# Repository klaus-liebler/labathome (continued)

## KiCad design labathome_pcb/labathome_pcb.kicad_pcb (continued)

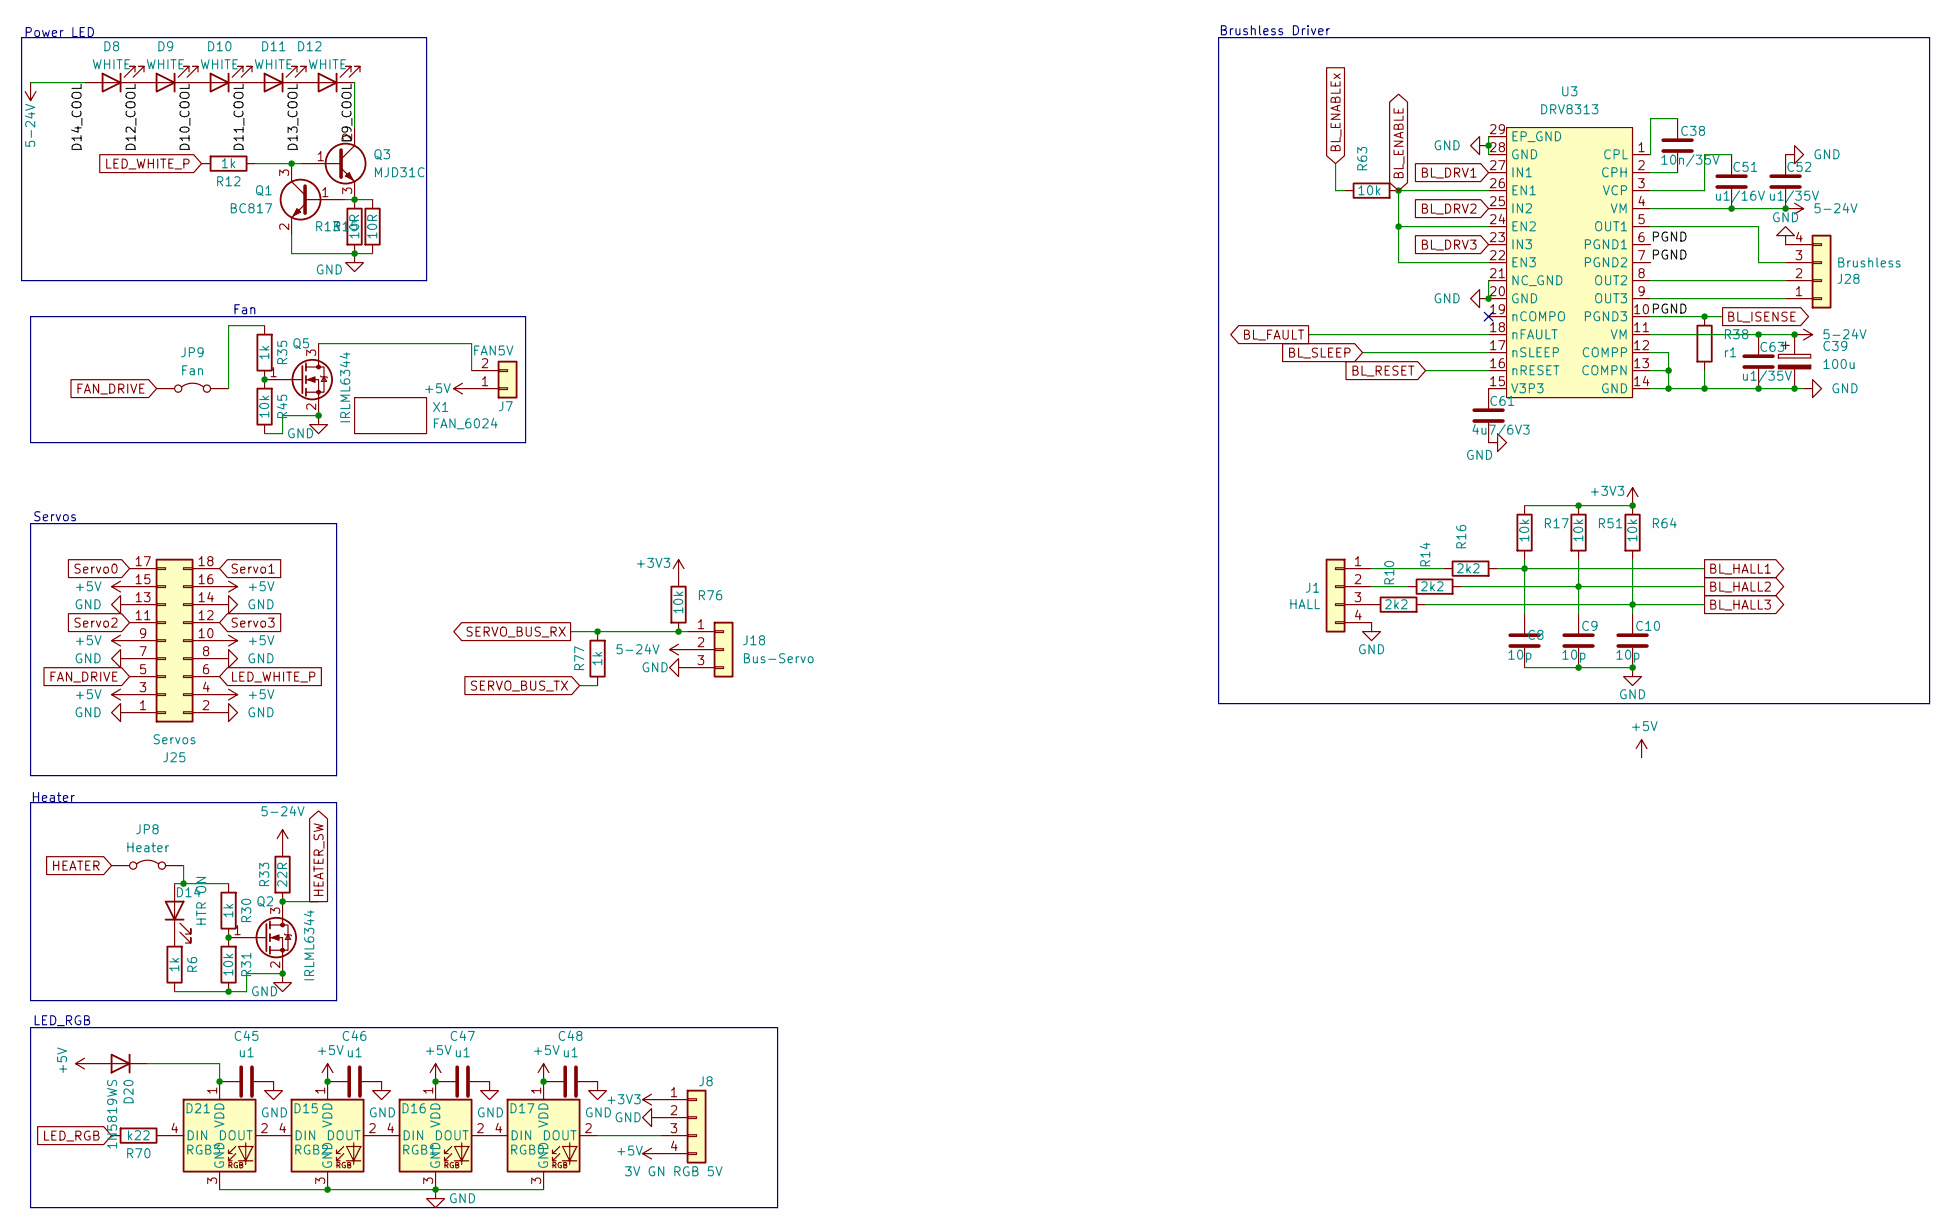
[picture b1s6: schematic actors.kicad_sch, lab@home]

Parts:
C8, C9, C10: 10p; C_0402_1005Metric; MPN CL05C100JB5NNNC
C38: 10n/35V; C_0402_1005Metric; MPN CL05B103KB5NNNC
C39: 100u; CP_Elec_6.3x5.4; MPN RST100UF35V009
C45, C46, C47, C48: u1; C_0201_0603Metric; MPN GRM033R61A104KE15D
C51: u1/16V; C_0603_1608Metric; MPN CC0603KRX7R9BB104
C52, C63: u1/35V; C_0603_1608Metric; MPN CC0603KRX7R9BB104
C61: 4u7/6V3; C_0402_1005Metric; MPN CL05A475MP5NRNC
D8, D9, D10, D11, D12: WHITE; LED_PLCC_2835_Handsoldering; MPN HL-A-2835D46W-S1-08-HR3(2800-3100K)
D14: HTR ON; LED_1206_3216Metric_ReverseMount; MPN LTST-C230KRKT
D15: RGB2; SK6812MINI-E_REV; MPN SK6812MINI-EA
D16: RGB1; SK6812MINI-E_REV; MPN SK6812MINI-EA
D17: RGB0; SK6812MINI-E_REV; MPN SK6812MINI-EA
D20: 1N5819WS; D_SOD-323; MPN 1N5819WS
D21: RGB3; SK6812MINI-E_REV; MPN SK6812MINI-EA
J1: HALL; PhoenixContact_MC_1,5_4-G-3.5_1x04_P3.50mm_Horizontal_small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; MPN KF2EDGR-3.5-4P
J7: FAN5V; JST_XH_B2B-XH-A_1x02_P2.50mm_Vertical; MPN B2B-XH-A(LF)(SN)
J8: 3V GN RGB 5V; PinHeader_1x04_P2.54mm_Vertical; MPN 2.54-1*4P
J18: Bus-Servo; Molex_SPOX_5267-03A_1x03_P2.50mm_Vertical; MPN 5267-03A / 22035035
J25: Servos; PinHeader_2x09_P2.54mm_Horizontal_SMD; MPN PZ254-2-09-WS
J28: Brushless; PhoenixContact_MC_1,5_4-G-3.5_1x04_P3.50mm_Horizontal_small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; MPN KF2EDGR-3.5-4P
JP8: Heater; SolderJumper-2_P1.3mm_Bridged2Bar_RoundedPad1.0x1.5mm
JP9: Fan; SolderJumper-2_P1.3mm_Bridged2Bar_RoundedPad1.0x1.5mm
Q1: BC817; SOT-23; MPN MMBT3904(RANGE:100-300)
Q2, Q5: IRLML6344; SOT-23; MPN AO3400
Q3: MJD31C; TO-252-2; MPN MJD31C
R6, R12, R30, R35: 1k; R_0402_1005Metric; MPN 0402WGF1001TCE
R10, R14, R16: 2k2; R_0402_1005Metric; MPN 0402WGF2201TCE
R13, R15: 10R; R_1206_3216Metric; MPN 1206W4F100JT5E
R17, R31, R45, R51, R63, R64: 10k; R_0201_0603Metric; MPN 0201WMF1002TEE
R33: 22R; Resistor_100W
R38: r1; R_1206_3216Metric; MPN FRM121WFR100TM
R70: k22; R_0402_1005Metric; MPN 0402WGF2200TCE
R76: 10k; R_0805_2012Metric_Pad1.20x1.40mm_HandSolder
R77: 1k; R_0805_2012Metric_Pad1.20x1.40mm_HandSolder
U3: DRV8313; HTSSOP-28-1EP_4.4x9.7mm_P0.65mm_EP2.85x5.4mm_ThermalVias; MPN DRV8313PWPR
X1: FAN_6024

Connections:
5-24V: C39.1, C51.2, C52.2, C63.1, D8.2 (A), J18.2, R33.1, U3.4 (VM), U3.11 (VM); also elsewhere on the board
+3V3: J8.1, R17.1, R51.1, R64.1, R76.1; also elsewhere on the board
+5V: C46.2, C47.2, C48.2, D15.1 (VDD), D16.1 (VDD), D17.1 (VDD), D20.2 (A), J7.1, J8.4, J25.3, J25.4, J25.9, J25.10, J25.15, J25.16; also elsewhere on the board
/actors/D9_COOL: D12.1 (K), Q3.2 (C)
/actors/D10_COOL: D9.1 (K), D10.2 (A)
/actors/D11_COOL: D10.1 (K), D11.2 (A)
/actors/D12_COOL: D8.1 (K), D9.2 (A)
/actors/D13_COOL: D11.1 (K), D12.2 (A)
ADC0_U1T: R77.1; also elsewhere on the board
ADC1_U1R: J18.1, R76.2, R77.2; also elsewhere on the board
BL_DRV1: U3.27 (IN1); also elsewhere on the board
BL_DRV2: U3.25 (IN2); also elsewhere on the board
BL_DRV3: U3.23 (IN3); also elsewhere on the board
BL_ENABLE: R63.2, U3.22 (EN3), U3.24 (EN2), U3.26 (EN1)
BL_ENABLEx: R63.1; also elsewhere on the board
BL_FAULT: U3.18 (nFAULT); also elsewhere on the board
BL_HALL1: C8.1, R16.2, R17.2; also elsewhere on the board
BL_HALL2: C9.1, R14.2, R51.2; also elsewhere on the board
BL_HALL3: C10.1, R10.2, R64.2; also elsewhere on the board
BL_ISENSE: R38.1, U3.6 (PGND1), U3.7 (PGND2), U3.10 (PGND3); also elsewhere on the board
BL_RESET: U3.16 (nRESET); also elsewhere on the board
BL_SLEEP: U3.17 (nSLEEP); also elsewhere on the board
FAN_DRIVE: J25.5, JP9.1 (A); also elsewhere on the board
GND: C8.2, C9.2, C10.2, C39.2, C45.1, C46.1, C47.1, C48.1, C52.1, C61.2, C63.2, D15.3 (GND), D16.3 (GND), D17.3 (GND), D21.3 (GND), J1.4, J8.2, J18.3, J25.1, J25.2, J25.7, J25.8, J25.13, J25.14, J28.4, Q1.2 (E), Q2.2 (S), Q5.2 (S), R6.1, R13.2, R15.2, R31.1, R38.2, R45.1, U3.12 (COMPP), U3.13 (COMPN), U3.14 (GND), U3.20 (GND), U3.21 (NC_GND), U3.28 (GND), U3.29 (EP_GND); also elsewhere on the board
HEATER: JP8.1 (A); also elsewhere on the board
HEATER_SW: Q2.3 (D), R33.2
LED_RGB: R70.2; also elsewhere on the board
LED_WHITE_P: J25.6, R12.2; also elsewhere on the board
unnamed: D14.2 (A), JP8.2 (B), R30.2
unnamed: D14.1 (K), R6.2
unnamed: D15.4 (DIN), D21.2 (DOUT)
unnamed: D15.2 (DOUT), D16.4 (DIN)
unnamed: D16.2 (DOUT), D17.4 (DIN)
unnamed: D17.2 (DOUT), J8.3
unnamed: C45.2, D20.1 (K), D21.1 (VDD)
unnamed: D21.4 (DIN), R70.1
unnamed: J1.1, R16.1
unnamed: J1.2, R14.1
unnamed: J1.3, R10.1
unnamed: J7.2, Q5.3 (D)
unnamed: J28.1, U3.9 (OUT3)
unnamed: J28.2, U3.8 (OUT2)
unnamed: J28.3, U3.5 (OUT1)
unnamed: JP9.2 (B), R35.2
unnamed: Q1.1 (B), Q3.3 (E), R13.1, R15.1
unnamed: Q1.3 (C), Q3.1 (B), R12.1
unnamed: Q2.1 (G), R30.1, R31.2
unnamed: Q5.1 (G), R35.1, R45.2
unnamed: C38.2, U3.2 (CPH)
unnamed: C38.1, U3.1 (CPL)
unnamed: C61.1, U3.15 (V3P3)
unnamed: C51.1, U3.3 (VCP)
STEPPER_DIR1: J25.17; also elsewhere on the board
STEPPER_STEP1: J25.18; also elsewhere on the board
STEPPER_STEP2: J25.11; also elsewhere on the board
STEPPER_STEP3: J25.12; also elsewhere on the board

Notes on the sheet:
Brushless Driver
Servos
Power LED
Heater
Fan
LED_RGB

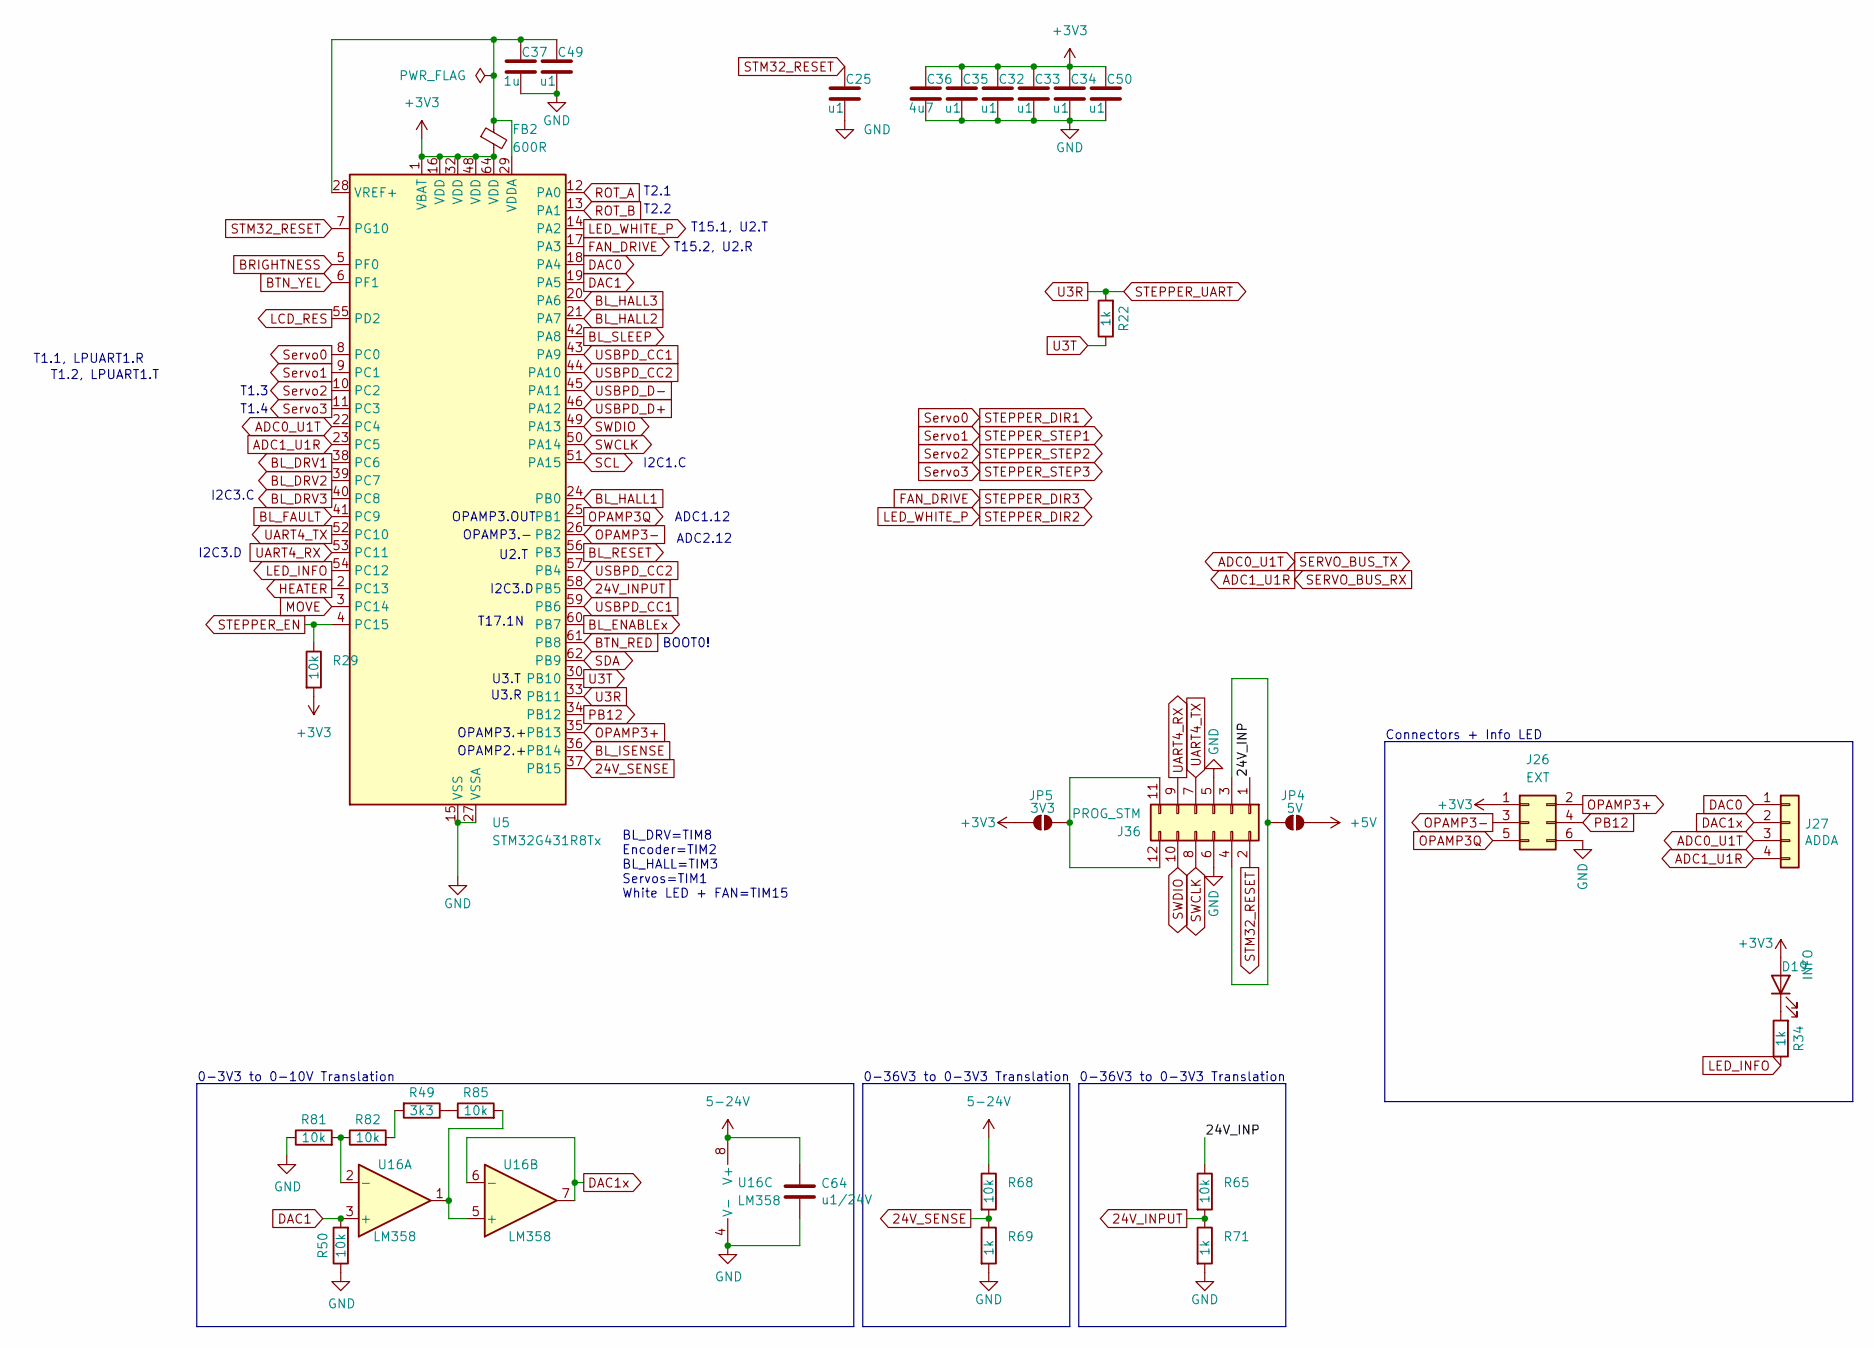
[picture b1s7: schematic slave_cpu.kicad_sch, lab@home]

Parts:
C25, C32, C33, C34, C35, C49, C50: u1; C_0201_0603Metric; MPN GRM033R61A104KE15D
C36: 4u7; C_0402_1005Metric; MPN CL05A475MP5NRNC
C37: 1u; C_0402_1005Metric; MPN CL05A105KA5NQNC
C64: u1/24V; C_0603_1608Metric; MPN CC0603KRX7R9BB104
D19: INFO; LED_1206_3216Metric_ReverseMount; MPN LTST-C230KRKT
FB2: 600R; L_0603_1608Metric; MPN BLM18AG601SN1D
J26: EXT; PinHeader_2x03_P2.54mm_Vertical; MPN PZ254V-12-6P
J27: ADDA; PhoenixContact_MC_1,5_4-G-3.5_1x04_P3.50mm_Horizontal_small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; MPN KF2EDGR-3.5-4P
J36: PROG_STM; PinSocket_2x06_P2.54mm_Vertical_SMD; MPN PZ254-2-06-S
JP4: 5V; SolderJumper-2_P1.3mm_Open_RoundedPad1.0x1.5mm
JP5: 3V3; SolderJumper-2_P1.3mm_Open_RoundedPad1.0x1.5mm
R22, R34, R69, R71: 1k; R_0402_1005Metric; MPN 0402WGF1001TCE
R29, R50, R65, R68, R81, R82, R85: 10k; R_0201_0603Metric; MPN 0201WMF1002TEE
R49: 3k3; R_0402_1005Metric; MPN 0402WGF3301TCE
U5: STM32G431R8Tx; LQFP-64_10x10mm_P0.5mm; MPN STM32G431RBT6
U16: LM358; SOIC-8_3.9x4.9mm_P1.27mm; MPN LM358DT

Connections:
5-24V: C64.2, R68.1, U16.8 (V+); also elsewhere on the board
24V_INPUT: R65.2, R71.1, U5.58 (PB5)
24V_SENSE: R68.2, R69.1, U5.37 (PB15)
+3V3: C32.1, C33.1, C34.1, C35.1, C36.1, C50.1, D19.2 (A), FB2.2, J26.1, JP5.1 (A), R29.2, U5.1 (VBAT), U5.16 (VDD), U5.32 (VDD), U5.48 (VDD), U5.64 (VDD); also elsewhere on the board
+5V: JP4.2 (B); also elsewhere on the board
/slave_cpu/24V_INP: J36.1, R65.1
ADC0_U1T: J27.3, U5.22 (PC4); also elsewhere on the board
ADC1_U1R: J27.4, U5.23 (PC5); also elsewhere on the board
BL_DRV1: U5.38 (PC6); also elsewhere on the board
BL_DRV2: U5.39 (PC7); also elsewhere on the board
BL_DRV3: U5.40 (PC8); also elsewhere on the board
BL_ENABLEx: U5.60 (PB7); also elsewhere on the board
BL_FAULT: U5.41 (PC9); also elsewhere on the board
BL_HALL1: U5.24 (PB0); also elsewhere on the board
BL_HALL2: U5.21 (PA7); also elsewhere on the board
BL_HALL3: U5.20 (PA6); also elsewhere on the board
BL_ISENSE: U5.36 (PB14); also elsewhere on the board
BL_RESET: U5.56 (PB3); also elsewhere on the board
BL_SLEEP: U5.42 (PA8); also elsewhere on the board
BRIGHTNESS: U5.5 (PF0); also elsewhere on the board
BTN_RED: U5.61 (PB8); also elsewhere on the board
BTN_YEL: U5.6 (PF1); also elsewhere on the board
DAC0: J27.1, U5.18 (PA4)
DAC1: R50.2, U5.19 (PA5), U16.3 (+)
DAC1x: J27.2, U16.6 (-), U16.7
FAN_DRIVE: U5.17 (PA3); also elsewhere on the board
GND: C25.2, C32.2, C33.2, C34.2, C35.2, C36.2, C37.2, C49.2, C50.2, C64.1, J26.6, J36.5, J36.6, R50.1, R69.2, R71.2, R81.1, U5.15 (VSS), U5.27 (VSSA), U5.31 (VSS), U5.47 (VSS), U5.63 (VSS), U16.4 (V-); also elsewhere on the board
HEATER: U5.2 (PC13); also elsewhere on the board
LCD_RES: U5.55 (PD2); also elsewhere on the board
LED_INFO: R34.1, U5.54 (PC12)
LED_WHITE_P: U5.14 (PA2); also elsewhere on the board
MOVE: U5.3 (PC14); also elsewhere on the board
unnamed: D19.1 (K), R34.2
unnamed: J36.3, J36.4, JP4.1 (A)
unnamed: J36.11, J36.12, JP5.2 (B)
unnamed: R49.1, R85.1
unnamed: R49.2, R82.2
unnamed: C37.1, C49.1, FB2.1, U5.28 (VREF+), U5.29 (VDDA)
unnamed: R81.2, R82.1, U16.2 (-)
unnamed: R85.2, U16.1, U16.5 (+)
OPAMP3+: J26.2, U5.35 (PB13)
OPAMP3-: J26.3, U5.26 (PB2)
OPAMP3Q: J26.5, U5.25 (PB1)
PB12: J26.4, U5.34 (PB12)
ROT_A: U5.12 (PA0); also elsewhere on the board
ROT_B: U5.13 (PA1); also elsewhere on the board
SCL: U5.51 (PA15); also elsewhere on the board
SDA: U5.62 (PB9); also elsewhere on the board
STEPPER_DIR1: U5.8 (PC0); also elsewhere on the board
STEPPER_EN: R29.1, U5.4 (PC15); also elsewhere on the board
STEPPER_STEP1: U5.9 (PC1); also elsewhere on the board
STEPPER_STEP2: U5.10 (PC2); also elsewhere on the board
STEPPER_STEP3: U5.11 (PC3); also elsewhere on the board
STEPPER_UART: R22.2, U5.33 (PB11); also elsewhere on the board
STM32_RESET: C25.1, J36.2, U5.7 (PG10)
SWCLK: J36.8, U5.50 (PA14)
SWDIO: J36.10, U5.49 (PA13)
U3T: R22.1, U5.30 (PB10)
UART4_RX: J36.9, U5.53 (PC11)
UART4_TX: J36.7, U5.52 (PC10)
USBPD_CC1: U5.43 (PA9), U5.59 (PB6); also elsewhere on the board
USBPD_CC2: U5.44 (PA10), U5.57 (PB4); also elsewhere on the board
USBPD_D+: U5.46 (PA12); also elsewhere on the board
USBPD_D-: U5.45 (PA11); also elsewhere on the board

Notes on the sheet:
U2.T
T2.2
T17.1N
T2.1
T1.2, LPUART1.T
I2C3.D
T1.1, LPUART1.R
OPAMP3.+
BL_DRV=TIM8 Encoder=TIM2 BL_HALL=TIM3 Servos=TIM1 White LED + FAN=TIM15
T1.4
T15.2, U2.R
T1.3
0-36V3 to 0-3V3 Translation
U3.T
T15.1, U2.T
0-3V3 to 0-10V Translation
I2C3.C
U3.R
Connectors + Info LED
I2C1.C
ADC1.12
ADC2.12
BOOT0!
OPAMP2.+
OPAMP3.-
OPAMP3.OUT

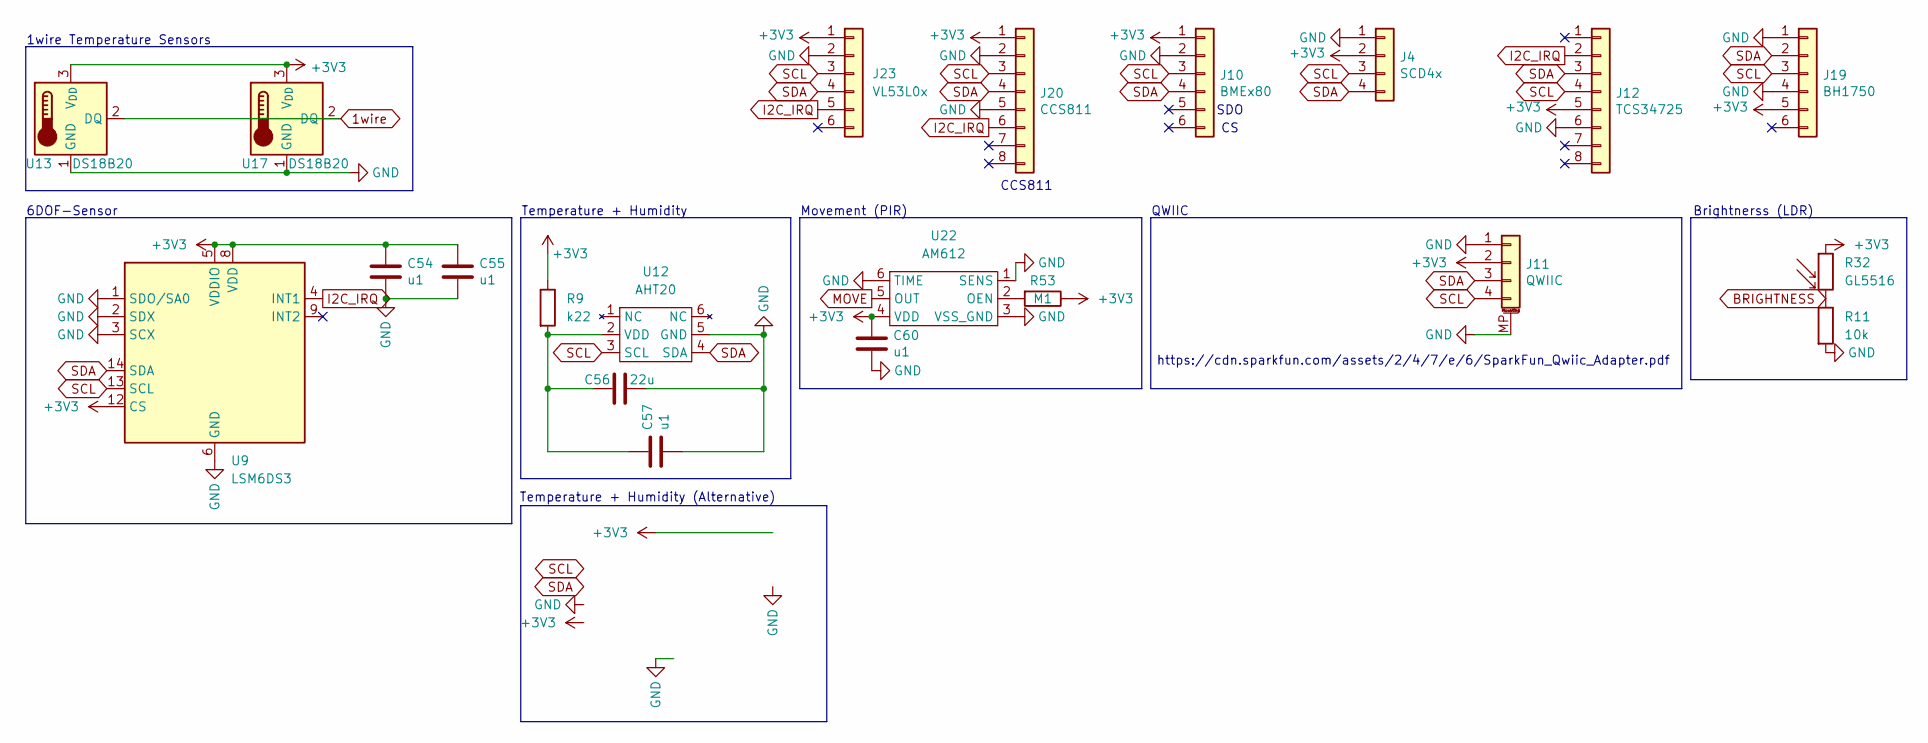
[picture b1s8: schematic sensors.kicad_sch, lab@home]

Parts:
C54, C55, C57, C60: u1; C_0201_0603Metric; MPN GRM033R61A104KE15D
C56: 22u; C_0603_1608Metric; MPN CL10A226MP8NUNE
J4: SCD4x; PinSocket_1x04_P2.54mm_Vertical; MPN 2.54-1*4P
J10: BMEx80; PinSocket_1x06_P2.54mm_Vertical; MPN 2.54-1*6P
J11: QWIIC; JST_SH_SM04B-SRSS-TB_1x04-1MP_P1.00mm_Horizontal; MPN SM04B-SRSS-TB(LF)(SN)
J12: TCS34725; PinSocket_1x08_P2.54mm_Vertical; MPN 2.54-1*8P
J19: BH1750; PinSocket_1x06_P2.54mm_Vertical; MPN 2.54-1*6P
J20: CCS811; PinSocket_1x08_P2.54mm_Vertical; MPN 2.54-1*8P
J23: VL53L0x; PinSocket_1x06_P2.54mm_Vertical; MPN 2.54-1*6P
R9: k22; R_0402_1005Metric; MPN 0402WGF2200TCE
R11: 10k; R_0201_0603Metric; MPN 0201WMF1002TEE
R32: GL5516; R_LDR_5.1x4.3mm_P3.4mm_Vertical; MPN GL5516
R53: M1; R_0201_0603Metric; MPN 0201WMF1003TEE
U9: LSM6DS3; LGA-14_3x2.5mm_P0.5mm_LayoutBorder3x4y; MPN LSM6DS3TR-C
U12: AHT20; AHT21; MPN AHT20
U13, U17: DS18B20; TO-92_HandSolder; MPN DS18B20
U22: AM612; MPN BS612

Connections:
1wire: U13.2 (DQ), U17.2 (DQ); also elsewhere on the board
+3V3: C54.2, C55.2, C60.2, J4.2, J10.1, J11.2, J12.5, J19.5, J20.1, J23.1, R9.1, R32.1, R53.1, U9.5 (VDDIO), U9.8 (VDD), U9.12 (CS), U13.3 (V_{DD}), U17.3 (V_{DD}), U22.4 (VDD); also elsewhere on the board
BRIGHTNESS: R11.1, R32.2; also elsewhere on the board
GND: C54.1, C55.1, C56.2, C57.1, C60.1, J4.1, J10.2, J11.1, J11.MP (MountPin), J12.6, J19.1, J19.4, J20.2, J20.5, J23.2, R11.2, U9.1 (SDO/SA0), U9.2 (SDX), U9.3 (SCX), U9.6 (GND), U9.7 (GND), U12.5 (GND), U13.1 (GND), U17.1 (GND), U22.1 (SENS), U22.3 (VSS_GND), U22.6 (TIME); also elsewhere on the board
I2C_IRQ: J12.2, J20.6, J23.5, U9.4 (INT1); also elsewhere on the board
MOVE: U22.5 (OUT); also elsewhere on the board
unnamed: C56.1, C57.2, R9.2, U12.2 (VDD)
unnamed: R53.2, U22.2 (OEN)
SCL: J4.3, J10.3, J11.4, J12.4, J19.3, J20.3, J23.3, U9.13 (SCL), U12.3 (SCL); also elsewhere on the board
SDA: J4.4, J10.4, J11.3, J12.3, J19.2, J20.4, J23.4, U9.14 (SDA), U12.4 (SDA); also elsewhere on the board

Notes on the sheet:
Brightnerss (LDR)
https://cdn.sparkfun.com/assets/2/4/7/e/6/SparkFun_Qwiic_Adapter.pdf
CCS811
Temperature + Humidity
Temperature + Humidity (Alternative)
Movement (PIR)
6DOF-Sensor
QWIIC
1wire Temperature Sensors
SDO

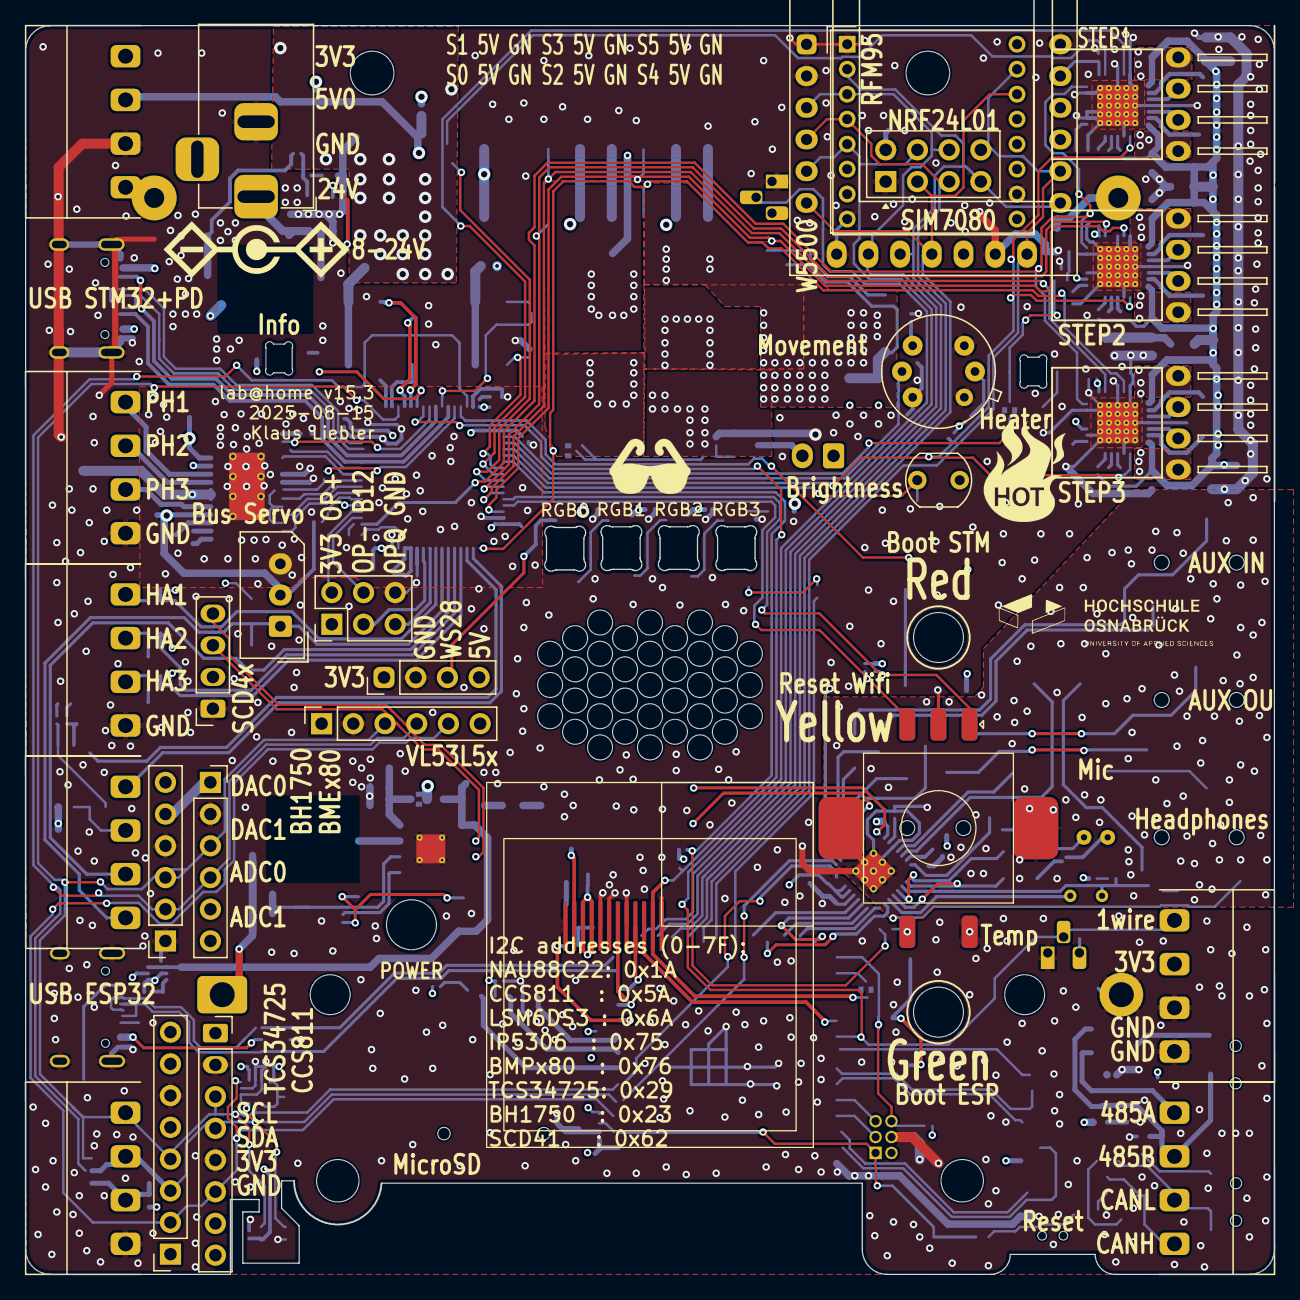
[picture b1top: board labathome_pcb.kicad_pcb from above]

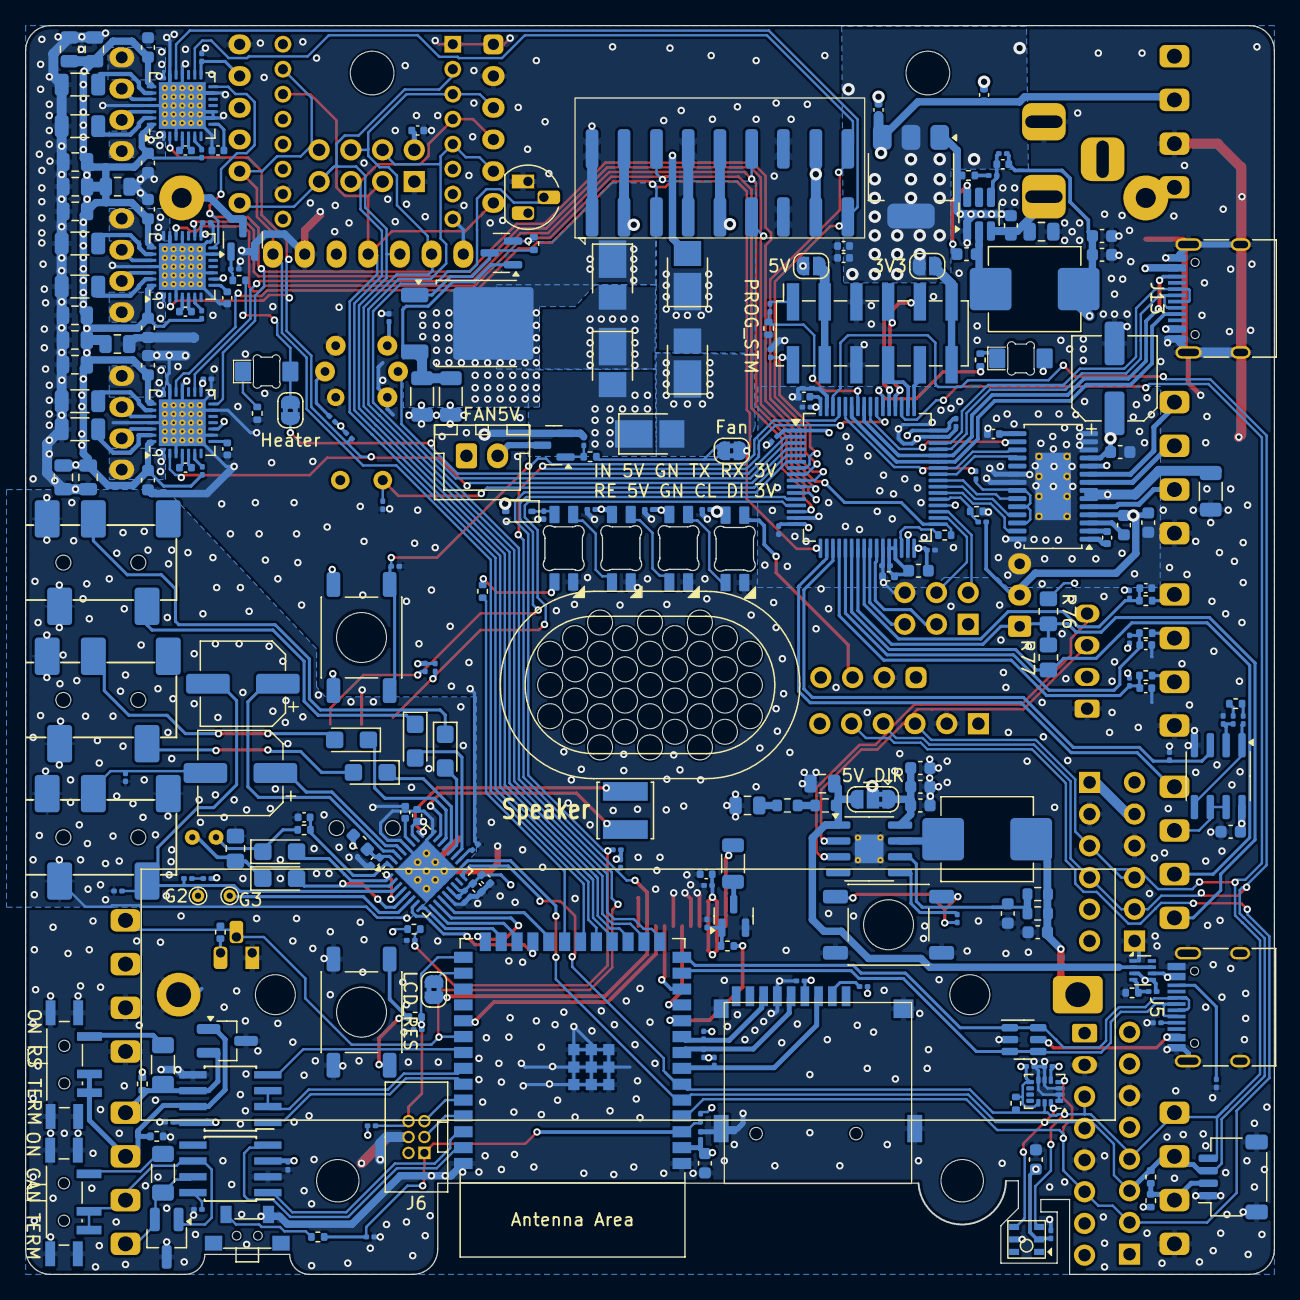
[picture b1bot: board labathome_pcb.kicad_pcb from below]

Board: 4 copper layers, 100.0 x 100.0 mm, 289 parts (256 on the bottom side), 217 nets.

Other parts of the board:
DRAWING1: Polarity; barrel_jack_positive_polarity

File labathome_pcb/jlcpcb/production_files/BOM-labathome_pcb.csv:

Comment,Designator,Footprint,LCSC,Quantity
56p,C82,C_0402_1005Metric,C107007,1
1k,"R12,R22,R30,R34,R35,R42,R5,R6,R69,R71,R74,R8",R_0402_1005Metric,C11702,12
SN65HVD230,U7,SOIC-8_3.9x4.9mm_Pitch1.27mm_handsolder,C12084,1
HTR ON,"D14,D19",LED_1206_3216Metric_ReverseMount,C125107,2
2u2,"C70,C73,C94",C_0402_1005Metric,C12530,3
u1/16V,"C51,C52,C63,C64,C68,C76,C79,C81,C86,C89,C92,C98",C_0603_1608Metric,C14663,12
10n/35V,C38,C_0402_1005Metric,C15195,1
USB STM32,"J13,J5",USB_C_Receptacle_HRO_TYPE-C-31-M-12_smaller,C165948,2
10R,"R13,R15,R78",R_1206_3216Metric,C17903,3
1N5819WS,D20,D_SOD-323,C191023,1
TPS54202DDC,U27,SOT-23-6_Handsoldering,C191884,1
600R,"FB1,FB2",L_0603_1608Metric,C19330,2
BC817,Q1,SOT-23,C20526,1
WHITE,"D10,D11,D12,D8,D9",LED_PLCC_2835_Handsoldering,C210325,5
TMC2209,U14,QFN-28-1EP_5x5mm_P0.5mm_EP3.75x3.75mm_ThermalVias,C2150710,1
1R,"R28,R3,R47,R7",R_0603_1608Metric,C22936,4
4u7,"C12,C13,C14,C15,C21,C22,C36,C41,C43,C61",C_0402_1005Metric,C23733,10
k22,"R1,R40,R66,R70,R9",R_0402_1005Metric,C25091,5
2k2,"R10,R14,R16,R24",R_0402_1005Metric,C25879,4
3k3,"R43,R44,R48,R49,R73",R_0402_1005Metric,C25890,5
M1,"R25,R53,R54,R59",R_0201_0603Metric,C270364,4
5k1,"R18,R19",R_0201_0603Metric,C274341,2
AHT20,U12,AHT21,C2757850,1
MJD31C,Q3,TO-252-2,C27596,1
SRV05-4,U8,SOT-23-6,C2836319,1
ESP32-S3-WROOM-1,U4,ESP32-S3-WROOM-1,C2913204,1
Bus-Servo,J18,Molex_SPOX_5267-03A_1x03_P2.50mm_Vertical,C293315,1
IRLML6344,"Q2,Q5,Q6",SOT-23,C2938367,3
r1,"R38,R79,R80,R83,R84,R87,R88",R_1206_3216Metric,C2991271,7
TPS2116DRL,U18,SOT-583-8,C3235557,1
PROG_STM,J36,PinSocket_2x06_P2.54mm_Vertical_SMD,C3294464,1
10p,"C10,C8,C9",C_0402_1005Metric,C32949,3
AUX OUT,"J14,J16,J3",PJ-327A,C381135,3
Micro_SD_Card_Det1,J17,microSD push,C393941,1
STM32G431R8Tx,U5,LQFP-64_10x10mm_P0.5mm,C431633,1
10k,"R11,R17,R2,R21,R26,R27,R29,R31,R36,R37,R39,R4,R41,R45,R50,R51,R55,R56,R57,R58,R60,R61,R62,R63,R64,R65,R67,R68,R72,R75,R81,R82,R85",R_0201_0603Metric,C473048,33
100u,C39,CP_Elec_6.3x5.4,C4747966,1
IP5306_I2C,U2,HSOP-8-1EP_3.9x4.9mm_P1.27mm_EP2.3x2.3mm_ThermalVias,C488349,1
Servos,J25,PinHeader_2x09_P2.54mm_Horizontal_SMD,C5149359,1
1u,"C37,C42,C44,C59,C67",C_0402_1005Metric,C52923,5
Reset,SW1,"Button_2x4x3,5_handsolder",C5373430,1
RGB2,"D15,D16,D17,D21",SK6812MINI-E_REV,C5378731,4
POWER,"SW5,SW7,SW8",SW_Push_1P1T_NO_6x6mm_H6.5mm_Reverse,C541960,3
10u,"C1,C4,C80",C_0805_2012Metric,C6119888,3
22u/35V,"C102,C103,C104,C69,C72,C77,C78,C85,C88,C93,C96,C97",C_0805_2012Metric,C6119901,12
AMS1117,U11,SOT-223-3_TabPin2,C6186,1
MAX3485,U1,SOIC-8_3.9x4.9mm_Pitch1.27mm_handsolder,C668205,1
1u,"C16,C17,C20,C23,C24,C62",CP_EIA-3216-10_Kemet-I,C7174,6
u1,"C11,C120,C2,C25,C26,C27,C3,C32,C33,C34,C35,C40,C45,C46,C47,C48,C49,C5,C50,C53,C54,C55,C57,C58,C60,C65,C66,C75,C87,C90,C91",C_0201_0603Metric,C76934,31
22n/50V,"C71,C74,C95",C_0402_1005Metric,C77023,3
22u,"C28,C29,C30,C31,C56,C6,C7,C83,C84",C_0603_1608Metric,C86295,9
220u,"C18,C19",CP_Elec_6.3x5.4,C88673,2
NAU8822,U10,QFN-32-1EP_5x5mm_P0.5mm_EP3.6x3.6mm_ThermalVias,C914209,1
DRV8313,U3,HTSSOP-28-1EP_4.4x9.7mm_P0.65mm_EP2.85x5.4mm_ThermalVias,C92482,1
LM358,U16,SOIC-8_3.9x4.9mm_P1.27mm,C9418,1
LSM6DS3,U9,LGA-14_3x2.5mm_P0.5mm_LayoutBorder3x4y,C967633,1
